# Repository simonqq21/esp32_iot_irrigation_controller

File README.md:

# ESP32 WiFi-Enabled Relay

# Introduction
The ESP32 WiFi-enabled relay is a proof-of-concept project that allows the user to control multiple AC sockets connected to relays by either a physical button, web interface on a browser, repeating daily schedule, countdown timer, or with other programming languages from a server computer via a websocket connection.  

# Features
- Runs on an **ESP32**
- Three relays, but can be configured with more or less relays.
- Each relay functions independently of each other.
- Each relay has a **physical pushbutton** for **manual control** and **cycling through operating modes**, and a **status LED** to indicate its **operating mode** (either manual, daily timer, countdown timer, or disabled) and **current state** (either closed or open).
- The ESP32 can be **configured to connect to any WiFi hotspot** by configuring it from the browser of any mobile or desktop device, or **create its own hotspot** for standalone use.
- **Physical WiFi reset button** to reset the WiFi connection to factory defaults.
- **Web interface** accessible through the browser of any mobile or desktop device. 
- The web interface running on the browser communicates to the ESP32 via a **websocket connection**.
- Time is kept via a **real time clock (RTC)**, and can either be **set manually** or **synced automatically to network time protocol (NTP)**.
- All configuration is persistent and is saved to the flash of the ESP32. 

# Hardware 
## Hardware components
The ESP32 WiFi-enabled relay has the following hardware components:
- ESP32 
- 3.3V/5V relay module x3
- DS1307 RTC module
- LED x3 for relay status LEDs
- Momentary pushbutton x3 for relay control
- LED x1 for main status LED
- Momentary pushbutton x1 for WiFi reset pushbutton
- AC to 5V power supply module 
## Circuit Diagram
- **ESP32 PCB Circuit Diagram**

- **LEDs and Pushbuttons PCB Circuit Diagram**

- **WiFi Reset Pushbutton PCB Circuit Diagram**

## PCB Design 

- **ESP32 PCB**

- **LEDs and Pushbuttons PCB**

- **WiFi Reset Pushbutton PCB**

## Enclosure Design 

# Installation
## Prerequisite software: 
- VS Code
- PlatformIO extension for VS Code 
## Installation Procedure 
1. Download and install **VS Code**. 
2. Download the **PlatformIO extension** within the VS Code extension manager. 
3. Clone this project from Github.
4. Open the cloned project folder in VS Code.
5. Open the **PlatformIO toolbar** from the VS Code sidebar. Your editor must look like this:

6. Upload the program to the ESP32. Click on the **esp32doit-devkit-v1/General/Upload** option inside the PlatformIO toolbar. It might take a few minutes as PlatformIO downloads all the dependencies for the project.

7. Upload the filesystem image to the ESP32. Click on the **esp32doit-devkit-v1/Platform/Upload filesystem image** option inside the PlatformIO toolbar.

Installation complete. 

# Usage
## Relay Operating Modes
- **Manual mode** retains the state of the relay until the user changes it either on the web interface or the physical pushbutton.
- **Daily timer mode** allows the user to set multiple timeslots. Each timeslot has a start and end time which has a maximum duration of one day, and can be enabled or disabled. By default, the relay is open. When the current time falls within at least one enabled timeslot, the relay will be closed. 
- **Countdown timer** allows the user to set a countdown duration and manually start and stop the countdown timer. When the countdown timer is started, the relay will close until either the countdown timer reaches zero or is manually stopped, then the relay will remain open until the user restarts the countdown timer. The countdown duration is saved.
- **Disabled** - the relay is always open.
## Relay Pushbutton
Each relay has a **physical pushbutton** for **manual control** and **cycling through operating modes**
- **Single click**
    - In manual mode, a single click toggles the relay state.
    - In countdown timer mode, a single click (re)starts and stops the countdown timer.
    - No effect in all other modes. 
- **Double click** 
    - In any mode, double click cycles through all modes (manual mode - daily timer mode - countdown timer mode - disabled).
## Relay Status LED 
Each relay has a **status LED** to indicate its **operating mode** (either manual, daily timer, countdown timer, or disabled) and **current state** (either relay closed or relay open).
- **Current operation mode**
    - The relay LED blinks a number of times to indicate the current operation mode. It blinks once if the relay is in manual mode, twice if the relay is in daily timer mode, thrice if the relay is in countdown timer mode, and none if the relay is disabled.
- **Current relay state**
    - After indicating the current operation mode, the LED will turn on if the relay is currently closed, and turn off if the relay is currently open. 
## Configuring the WiFi connection
The ESP32 WiFi-Enabled relay can either produce its own WiFi hotspot in **station mode**, or connect to a WiFi hotspot in **access point mode**.
- Upon startup, the ESP32 will attempt to connect to the stored WiFi SSID (and password, if the WiFi is password secured). If it does not connect successfully for any reason, such as a nonexistent SSID or an incorrect password, it will automatically switch to access point mode and start its WiFi hotspot, which is an open WiFi network so that the user can connect to it to either use as-is, or to configure it to connect to their desired WiFi network.
- When the ESP32 is in access point mode, the ESP32 is accessible by connecting to the open WiFi network with SSID **ESP32_wifi_manager** and entering *http://192.168.4.1:7777/wifi.html* into the URL bar of the web browser. This opens up the ESP32 WiFi manager page. 

- Clicking the **Connect** button will direct the browser into the WiFi connect menu. Here, the user enters a WiFi password (if the WiFi is password secured) and the desired last octet of the IP address which ranges from 0-255. The last octet is used to set the *static IP address* of the ESP32 in the WiFi network it connects to so that it will be straightfoward to find and address the ESP32 in the network. The port number input is ignored because the port has been hardcoded to *7777*.

- A **reset pushbutton** allows the user to manually reset the WiFi credentials stored on the ESP32 even without having network access to the ESP32 so that the ESP32 will be reset into access point mode and the user can reconfigure the WiFi connection. **Long-pressing** the WiFi reset pushbutton until the main status LED blinks three times resets the WiFi credentials and restarts the ESP32. 

## Web Interface
The **web interface** allows the user to change various settings, including but not limited to the device name, relay operating modes, and relay state.
- **If the ESP32 is connected to a WiFi hotspot**, the web interface is accessible through the link *http://router_IP_subnet.ESP32_IP_index:7777/*. For example, if your WiFi router's network range is 192.168.5.0 to 192.168.5.255 and you set the ESP32 to have an IP address index of 80, then the URL to access the web interface is *http://192.168.5.80:7777/*.
- **If the ESP32 is in access point mode**, then its IP address is hardcoded  to *192.168.4.1*, so the URL to access the web interface is *http://192.168.4.1:7777/*. 
- The web interface allows the user to change the following configuration:
    - ESP32 device name
    - System date and time
    - Automatically sync time or set time manually 
    - main status LED setting
    - Relay status LED setting
    - Relay operation mode
    - Relay state (in manual mode)
    - Relay timeslots (in daily timer mode)
    - Relay countdown timer duration (in countdown timer mode)
- The web interface also displays status and information.
    - System date and time
    - Relay status
    - All settings
- The web interface communicates to the ESP32 via a **websocket connection**. This allows multiple ESP32 units on the same WiFi network to be programmatically controlled with the websocket libraries of various programming languages such as Python. The formats of the websocket messages are specified in *lib/Websocket_module/Webserver_module.h*.

- Change the selected relay to view and manage its settings.

- Change the operation mode of the selected relay.

- When a relay is in **manual mode**, the relay state can be changed.

- When a relay is in **daily timer mode**, the start time, end time, duration, and enabled setting of each timeslot can be changed.

- When a relay is in **countdown timer mode**, the countdown timer duration in seconds can be changed and the countdown timer can be started and stopped.

- There are countdown timers in the relay status indicators that indicate how much time the relay countdown timer has left before the relay opens.

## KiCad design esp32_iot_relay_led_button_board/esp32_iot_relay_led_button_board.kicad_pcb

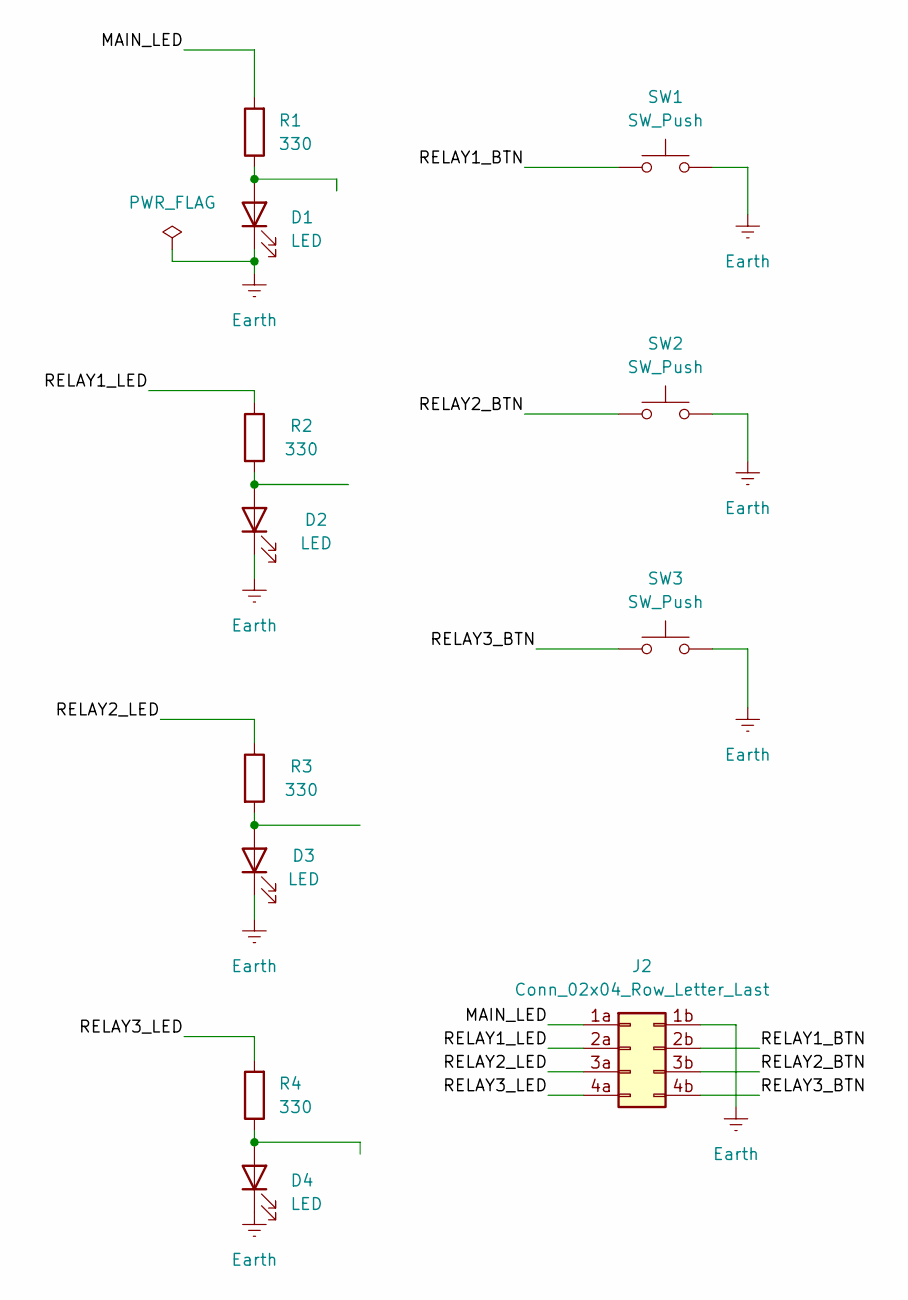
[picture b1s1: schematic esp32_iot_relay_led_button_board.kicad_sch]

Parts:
D1, D2, D3, D4: LED; LED_D5.0mm
J2: Conn_02x04_Row_Letter_Last; PinHeader_2x04_P2.54mm_Vertical_alphabetical
R1, R2, R3, R4: 330; R_Axial_DIN0207_L6.3mm_D2.5mm_P10.16mm_Horizontal
SW1, SW2, SW3: SW_Push; SW_SPST_Omron_B3F-40xx

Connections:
/MAIN_LED: J2.1a, R1.2
/RELAY1_BTN: J2.2b, SW1.1
/RELAY1_LED: J2.2a, R2.1
/RELAY2_BTN: J2.3b, SW2.1
/RELAY2_LED: J2.3a, R3.1
/RELAY3_BTN: J2.4b, SW3.1
/RELAY3_LED: J2.4a, R4.2
Earth: D1.1 (K), D2.1 (K), D3.1 (K), D4.1 (K), J2.1b, SW1.2, SW2.2, SW3.2
unnamed: D1.2 (A), R1.1
unnamed: D2.2 (A), R2.2
unnamed: D3.2 (A), R3.2
unnamed: D4.2 (A), R4.1

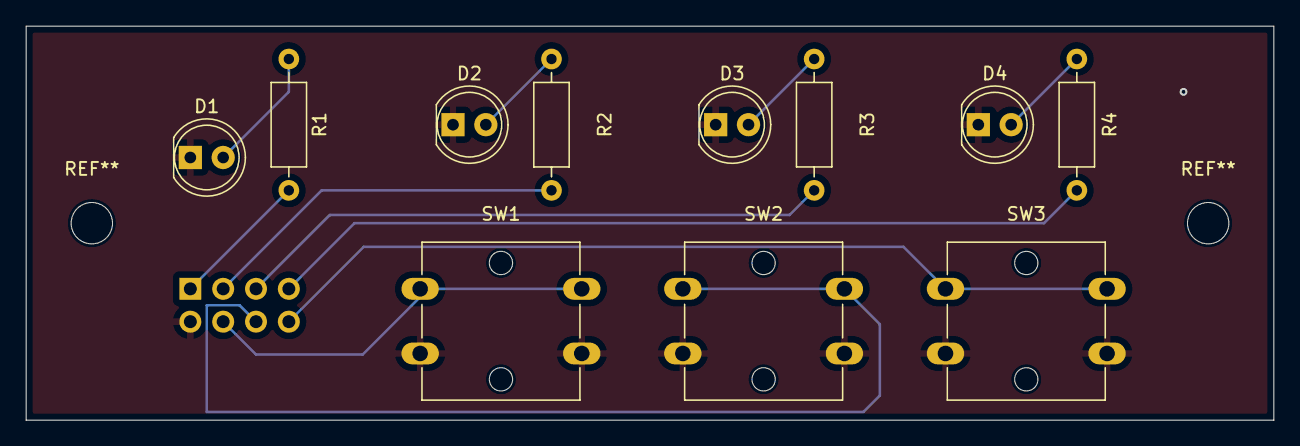
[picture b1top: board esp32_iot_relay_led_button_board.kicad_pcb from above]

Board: 2 copper layers, 96.5 x 30.5 mm, 12 parts (1 on the bottom side), 12 nets.

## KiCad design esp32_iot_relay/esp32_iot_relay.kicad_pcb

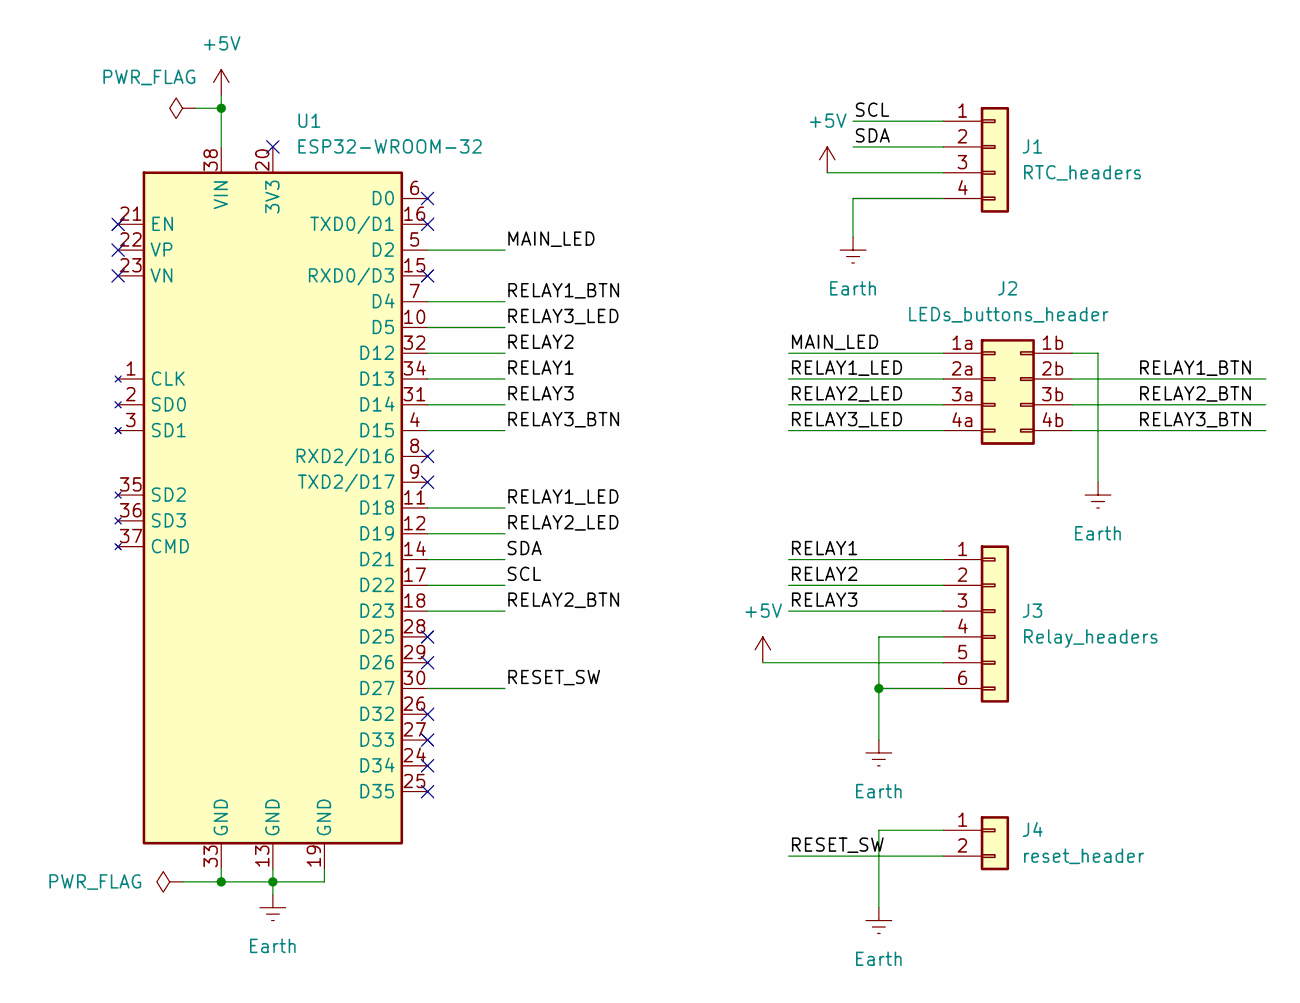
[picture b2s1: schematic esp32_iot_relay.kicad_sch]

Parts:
J1: RTC_headers; PinSocket_1x04_P2.54mm_Vertical
J2: LEDs_buttons_header; PinHeader_2x04_P2.54mm_Vertical_alphabetical
J3: Relay_headers; PinHeader_1x06_P2.54mm_Vertical
J4: reset_header; PinHeader_1x02_P2.54mm_Vertical
U1: ESP32-WROOM-32; esp32_doit_devkitv1_38pin

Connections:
+5V: J1.3, J3.5, U1.38 (VIN)
/MAIN_LED: J2.1a, U1.5 (D2)
/RELAY1: J3.1, U1.34 (D13)
/RELAY1_BTN: J2.2b, U1.7 (D4)
/RELAY1_LED: J2.2a, U1.11 (D18)
/RELAY2: J3.2, U1.32 (D12)
/RELAY2_BTN: J2.3b, U1.18 (D23)
/RELAY2_LED: J2.3a, U1.12 (D19)
/RELAY3: J3.3, U1.31 (D14)
/RELAY3_BTN: J2.4b, U1.4 (D15)
/RELAY3_LED: J2.4a, U1.10 (D5)
/RESET_SW: J4.2, U1.30 (D27)
/SCL: J1.1, U1.17 (D22)
/SDA: J1.2, U1.14 (D21)
Earth: J1.4, J2.1b, J3.4, J3.6, J4.1, U1.13 (GND), U1.19 (GND), U1.33 (GND)

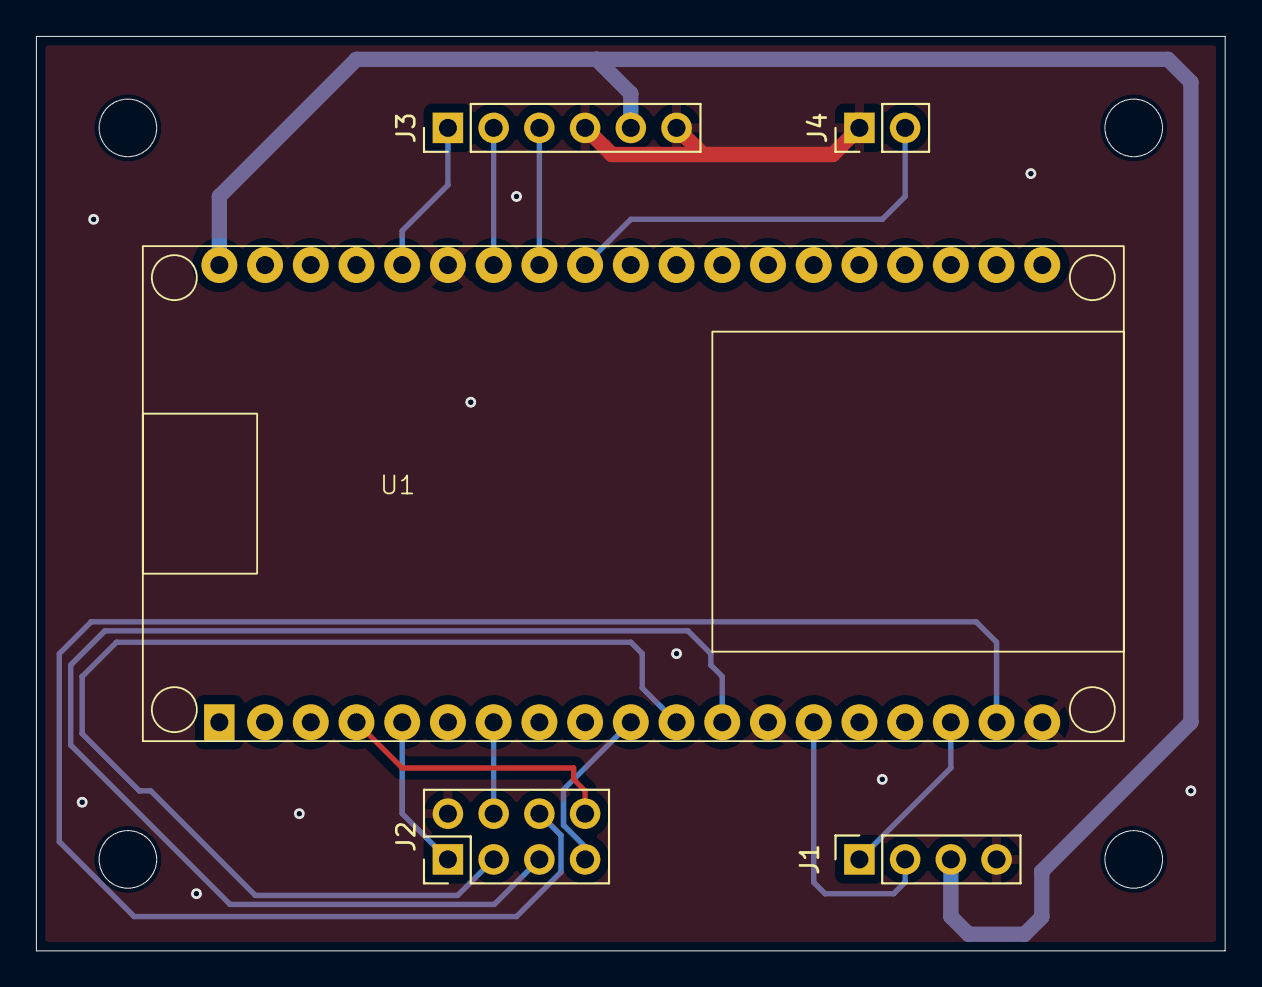
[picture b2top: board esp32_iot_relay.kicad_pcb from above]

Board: 2 copper layers, 66.0 x 50.8 mm, 5 parts (0 on the bottom side), 15 nets.

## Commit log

2024-09-03 button control for toggling timer enable and relay state
2024-09-03 button long press now resets wifi connection to factory default
2024-09-04 asdfasdf
2024-09-05 in updateTime, setGMTOffset was moved before updateRTCWithNTP to fix the bug of the GMT offset not being applied properly.
2024-09-11 creating wifi configuration page html and js
2024-09-13 basic wifi webpage functionality working
2024-09-17 created index html skeleton
2024-09-17 evuevueuv
2024-09-19 created wsMod.js ], working sendConnection
2024-09-19 added documentation to wifi.js
2024-09-19 completed wsMod.js and its documentation.
2024-09-20 added SSID name to connect menu in wifi.html
2024-09-20 aSDASD
2024-09-21 rearranged elements in index.html
2024-09-21 working relay status realtime update on browser
2024-09-24 updated NTP enable display
2024-09-25 added some more code to display values from the ESP32 to the browser Fixed bug in sending current relay states from ESP32 to browser
2024-09-25 asdfghjkl
2024-09-26 added code to update the duration of each timeslot
2024-09-26 added bugfix for relay state resetting to false in function call checkRelayIfOn
2024-09-26 Set the asyncwebserver _server in webserverModule into a pointer so I could set the port from eepromConfig
2024-09-26 updated class names for timeslots elements
2024-09-26 asdfghjklp
2024-09-27 asdfghjkl;
2024-09-27 completed event listener code for modifying timeslot startTime, endTime, and duration
2024-09-27 created function calculateEndTime
2024-09-27 It's working!!!!!!!!!!!1111111111111111111111!!!!!!!!!!!!!!!!!!!!!!!!
2024-09-27 made changes to wifi.js to use a template for wifi hotspot table rows instead of creating a new row manually for each wifi hotspot Used window.location.port to get port in javascript Fixed bug with p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
2024-09-27 added step 1 second to manualTimeInput
2024-09-30 fixed font size scaling issues with desktop and mobile fixed wifi hotspot loss behavior added comment describing expected behavior to webserver module header webserver works fine with wifi router but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
2024-09-30 fixed behavior of manual time input pinpointed the source of the watchdog reset, which is the ntp update when ntp is enabled and the wifi hotspot has no access to the NTP server
2024-09-30 tidied up the code in index.js manual time configuration now takes the system time upon webpage load Added comments to index.js
2024-09-30 resolved watchdog reset with ntp websockets with no internet Tidied up and put comments in main.cpp
2024-09-30 asdfghjkl;asdfghjkl
2024-09-30 todo
2024-10-01 fixed bug with automatic timer when a timeslot has startTime before 12AM, endTime after 12AM, and now after 12AM.
2024-10-03 removed interrupt from setFullOnOffTimes
2024-10-08 working countdown timer, toggle, start, and stop with button
2024-10-09 added operation mode setting input and countdown input div to html
2024-10-09 countdown timer feature now working with webpage GUI
2024-10-10 doremi
2024-10-10 revised EEPROMConfig to have multiple relay configs
2024-10-10 webserver module multiple relays WIP
2024-10-11 completed webserver module
2024-10-12 working button toggles, next is to revise the javascript so that the websocket methods can be tested.
2024-10-12 asdf
2024-10-12 updated html for multiple relays
2024-10-13 added multiple relay statuses to html
2024-10-14 multiple relay states working
2024-10-14 working disabled and manual control but bugs still present in schedule and countdown
2024-10-14 fixed bug with countdown start/stop and timeslots schedule mode, everything working so far after testing.
2024-10-15 fixed bug with relay config not saving uploaded fs to esp32 goal is to make minor UI fixes for ease of use
2024-10-16 added dynamic hostname and port in js files cleaned up code and added function documentation in index.js made a template div invisible in index.html
2024-10-16 fixed the annoying issue with the EEPROM not committing (changed all the shorts into ints) added wifi reset button and main status LED cuz moar LEDs cool
2024-10-16 v2 is functionally complete, added todo for v3
2024-10-18 ASDFV3
2024-10-18 improved status LED blinking behavior
2024-10-18 working v3 yay
2024-10-18 working v3 yay website save buttons are now disabled until any config is modified. status LEDs now flash out the operation mode of that relay.
2024-10-18 wifi password field set timeslot inputs event listener to enable relay config save button
2024-10-21 pcb files
2024-10-22 symbols for ESP32 boards
2024-10-22 completed schematic and passed ERC, basic footprint arrangements done.
2024-10-23 minor bug with relay start stop button on webpage
2024-10-23 completed main PCB currently working on leds_buttons_pcb
2024-10-24 completed led and button board
2024-10-24 completed reset button PCB
2024-10-27 print
2024-11-03 updated PCB designs to have standard breadboard spacing used mil spacing
2024-11-20 fix bug with the countdown timer start/stop button every time the relay selector is changed
2024-11-20 changed LED behavior to: Off: LED is totally off On: LED is totally on Blinking: LED blinks the current operation mode periodically, but is mostly off when the relay is off and mostly on when the rel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
2024-11-20 add a time remaining countdown beside each relay which appears when countdown mode and relay is activated It works well in softAP mode but lags in STA mode, maybe because of the latency of the mcu to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
2024-11-21 disabled wifi sleep for better latency
2025-01-04 README.md
2025-01-06 Completed README
